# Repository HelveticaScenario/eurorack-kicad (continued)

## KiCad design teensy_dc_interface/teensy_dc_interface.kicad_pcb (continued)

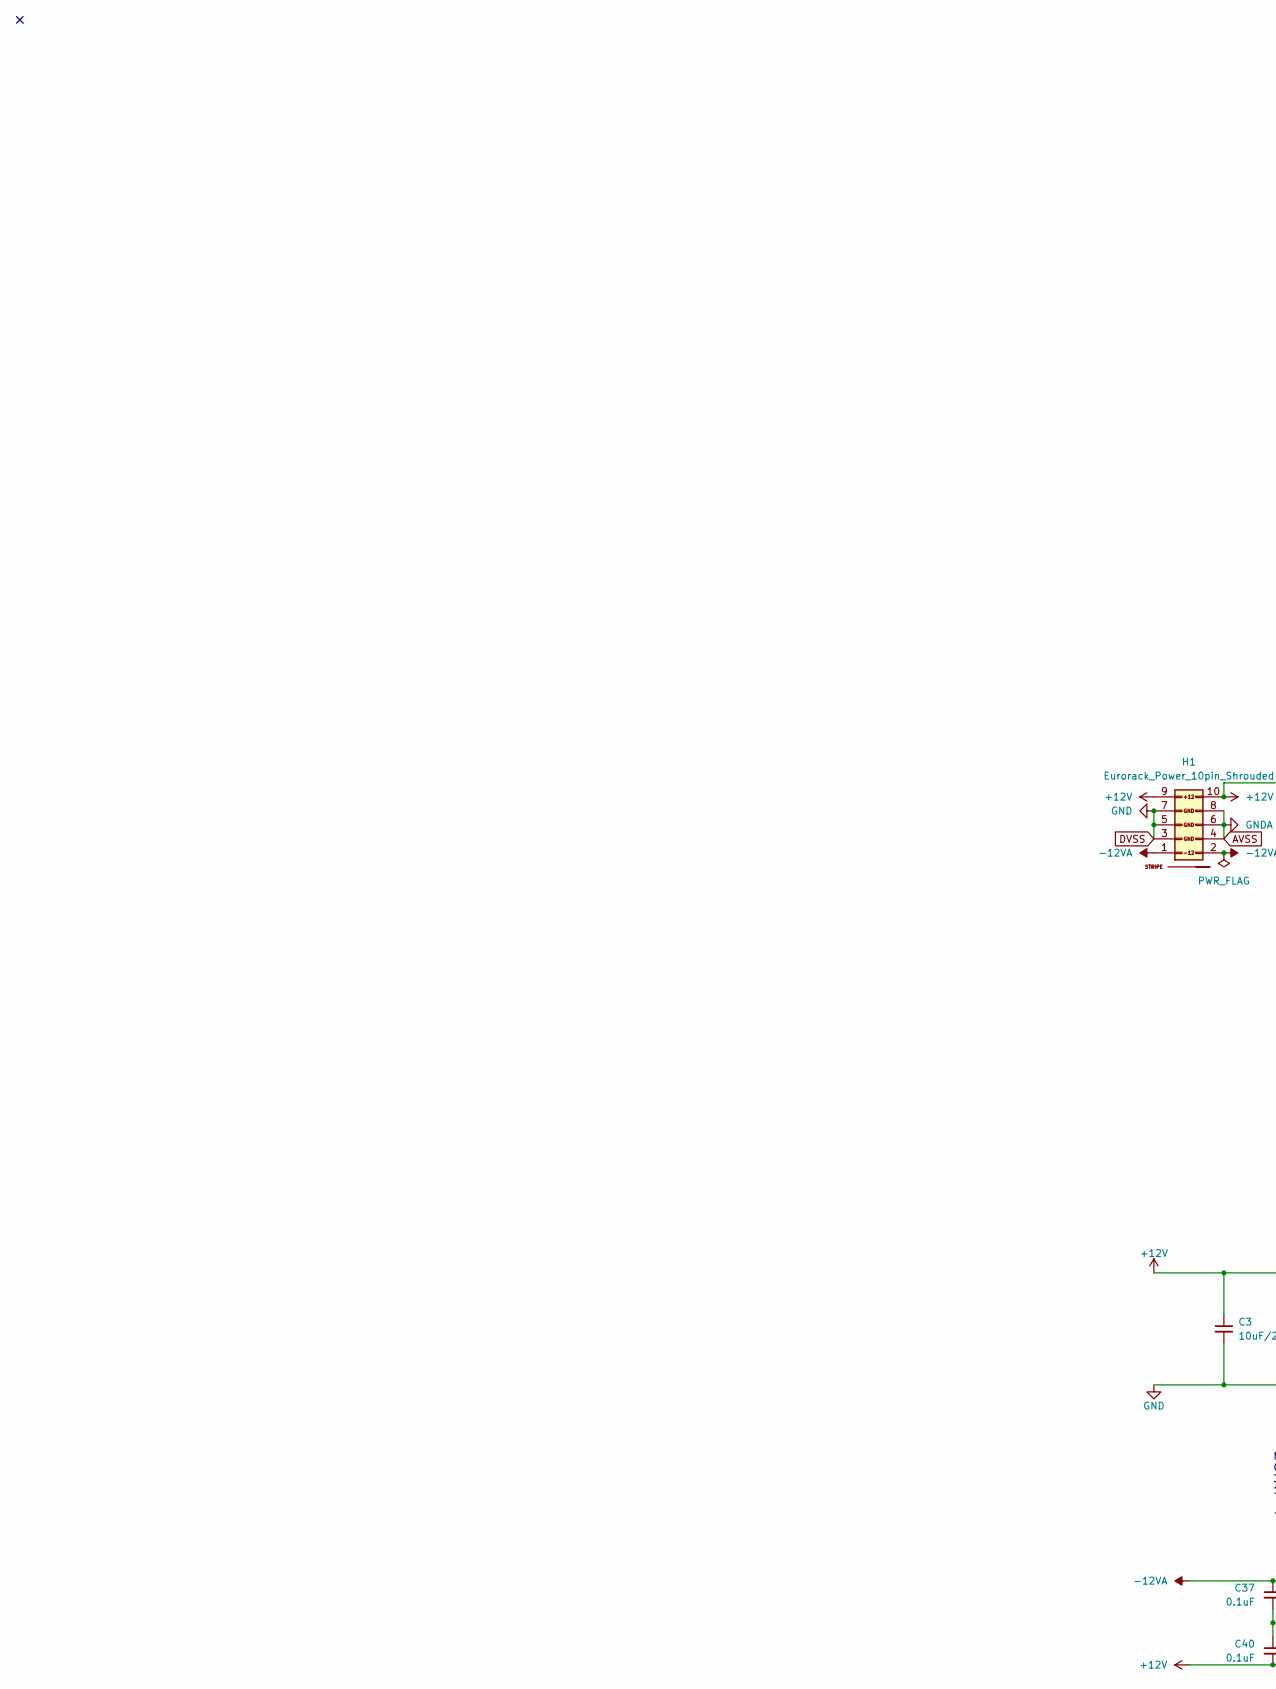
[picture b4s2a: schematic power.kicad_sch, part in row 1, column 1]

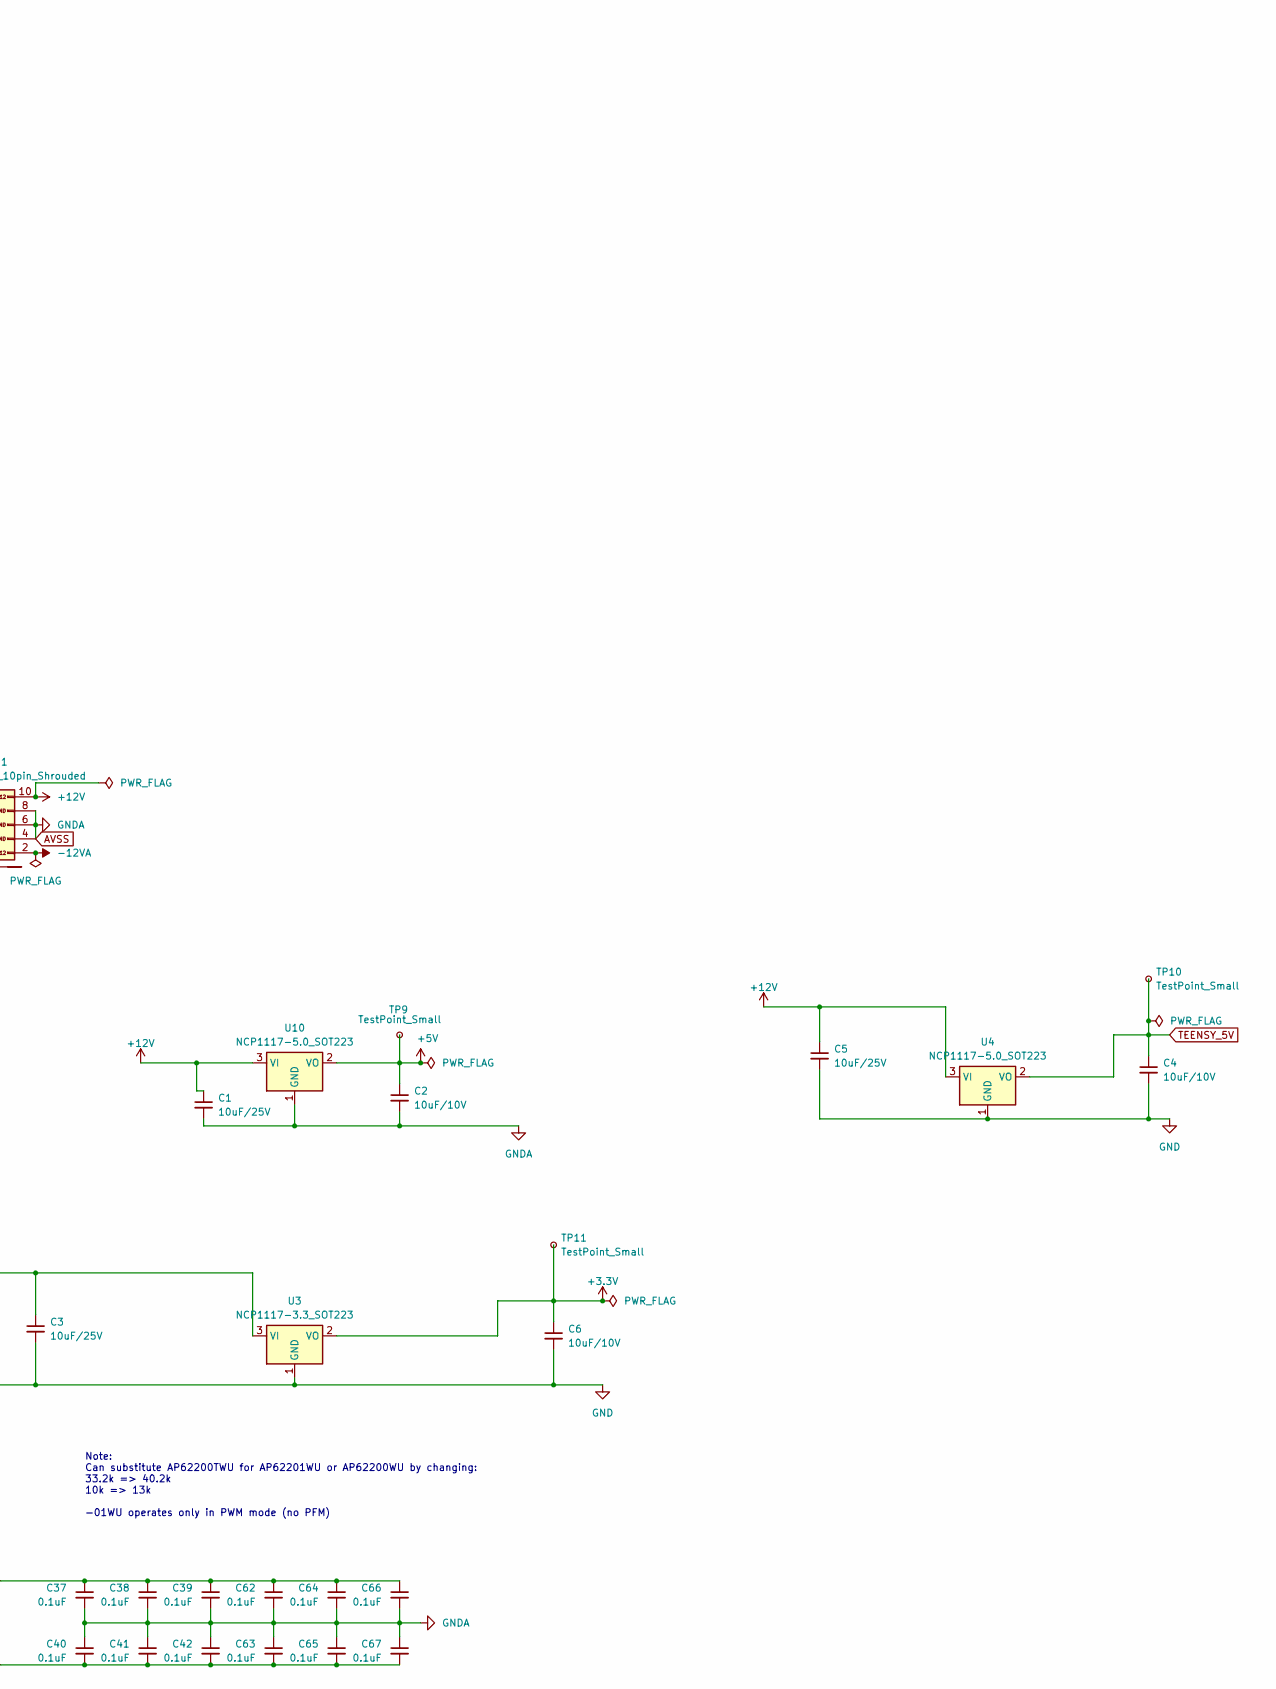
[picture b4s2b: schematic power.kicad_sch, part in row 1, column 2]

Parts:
C1, C3, C5: 10uF_0805_25V; C_0805; Part Number GRM21BR61E106MA73L; JLCPCB ID C15850
C2, C4, C6: 10uF_0603_10V; C_0603; Part Number GRM188R61A106KE69D; JLCPCB ID C19702
C37, C38, C39, C40, C41, C42, C62, C63, C64, C65, C66, C67: 0.1uF_0603_16V; C_0603; Part Number 0603YC104KAT2A; JLCPCB ID C14663
H1: Eurorack_Power_10pin_Shrouded; Pins_2x05_2.54mm_TH_EurorackPower_Shrouded; Part Number 61201021621
TP9, TP10, TP11: TestPoint_Small; TestPoint_Keystone_5005-5009_Compact
U3: NCP1117-3.3_SOT223; SOT-223-3_TabPin2
U4, U10: NCP1117-5.0_SOT223; SOT-223-3_TabPin2

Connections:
+12V: C1.1, C3.1, C5.1, C40.2, C41.2, C42.2, C63.2, C65.2, C67.2, H1.9 (+12V), H1.10 (+12V), U3.3 (VI), U4.3 (VI), U10.3 (VI); also elsewhere on the board
-12VA: C37.1, C38.1, C39.1, C62.1, C64.1, C66.1, H1.1 (-12V), H1.2 (-12V); also elsewhere on the board
AVDD: C2.1, TP9.1, U10.2 (VO); also elsewhere on the board
AVSS: C1.2, C2.2, C37.2, C38.2, C39.2, C40.1, C41.1, C42.1, C62.2, C63.1, C64.2, C65.1, C66.2, C67.1, H1.4 (GND), H1.6 (GND), H1.8 (GND), U10.1 (GND); also elsewhere on the board
DVSS: C3.2, C4.2, C5.2, C6.2, H1.3 (GND), H1.5 (GND), H1.7 (GND), U3.1 (GND), U4.1 (GND); also elsewhere on the board
TEENSY_5V: C4.1, TP10.1, U4.2 (VO); also elsewhere on the board
TVDD: C6.1, TP11.1, U3.2 (VO); also elsewhere on the board

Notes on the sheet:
Note: Can substitute AP62200TWU for AP62201WU or AP62200WU by changing: 33.2k => 40.2k 10k => 13k -01WU operates only in PWM mode (no PFM)

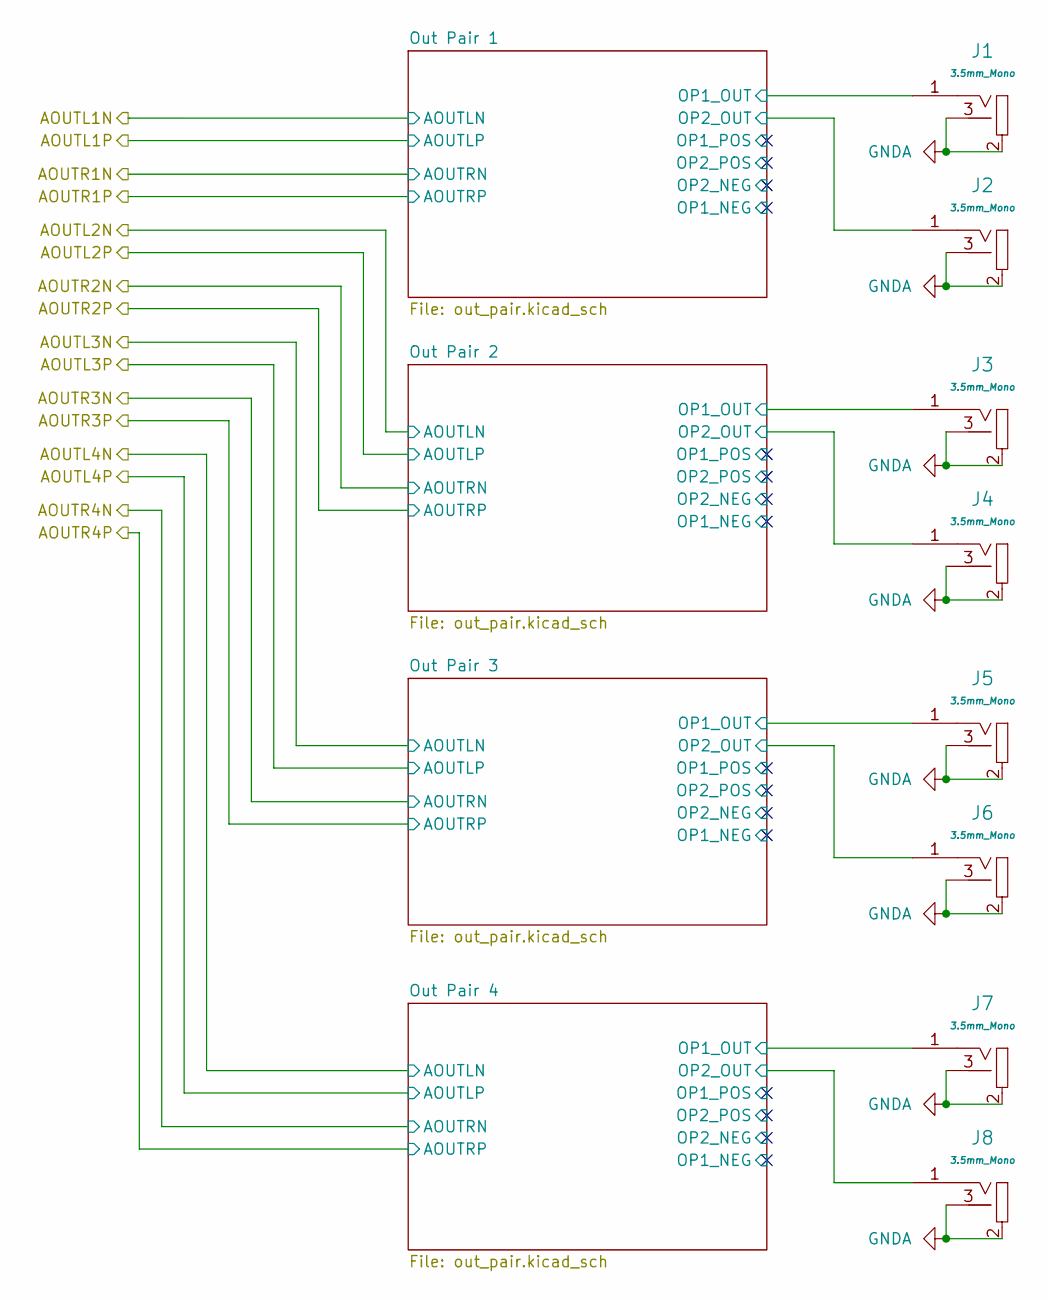
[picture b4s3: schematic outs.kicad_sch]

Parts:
J1: Chan 1 Out; EighthInch_PJ398SM; Part Number WQP-WQP518MA
J2: Chan 2 Out; EighthInch_PJ398SM; Part Number WQP-WQP518MA
J3: Chan 3 Out; EighthInch_PJ398SM; Part Number WQP-WQP518MA
J4: Chan 4 Out; EighthInch_PJ398SM; Part Number WQP-WQP518MA
J5: Chan 5 Out; EighthInch_PJ398SM; Part Number WQP-WQP518MA
J6: Chan 6 Out; EighthInch_PJ398SM; Part Number WQP-WQP518MA
J7: Chan 7 Out; EighthInch_PJ398SM; Part Number WQP-WQP518MA
J8: Chan 8 Out; EighthInch_PJ398SM; Part Number WQP-WQP518MA

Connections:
/Outs/Out Pair 1/OP1_OUT: J1.1 (SIG); also elsewhere on the board
/Outs/Out Pair 1/OP2_OUT: J2.1 (SIG); also elsewhere on the board
/Outs/Out Pair 2/OP1_OUT: J3.1 (SIG); also elsewhere on the board
/Outs/Out Pair 2/OP2_OUT: J4.1 (SIG); also elsewhere on the board
/Outs/Out Pair 3/OP1_OUT: J5.1 (SIG); also elsewhere on the board
/Outs/Out Pair 3/OP2_OUT: J6.1 (SIG); also elsewhere on the board
/Outs/Out Pair 4/OP1_OUT: J7.1 (SIG); also elsewhere on the board
/Outs/Out Pair 4/OP2_OUT: J8.1 (SIG); also elsewhere on the board
AVSS: J1.2 (SHEILD), J1.3 (SW), J2.2 (SHEILD), J2.3 (SW), J3.2 (SHEILD), J3.3 (SW), J4.2 (SHEILD), J4.3 (SW), J5.2 (SHEILD), J5.3 (SW), J6.2 (SHEILD), J6.3 (SW), J7.2 (SHEILD), J7.3 (SW), J8.2 (SHEILD), J8.3 (SW); also elsewhere on the board

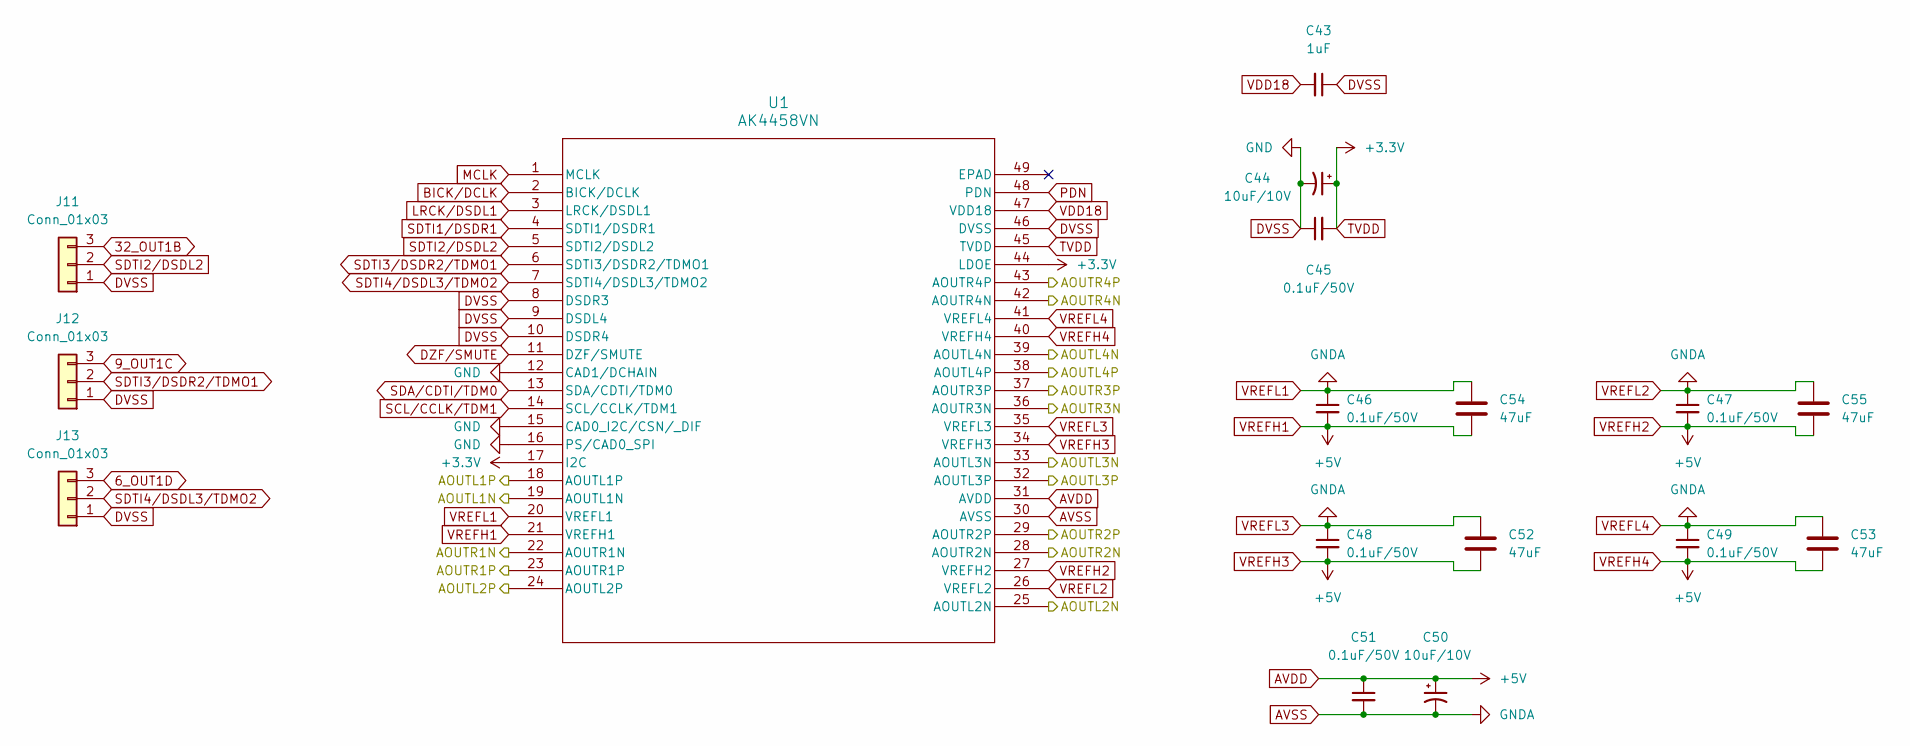
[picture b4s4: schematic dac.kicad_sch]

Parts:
C43: 1uF_0402_25V; C_0402; Part Number GMK105CC6105KV-F; JLCPCB ID C52923
C44, C50: 10uF_4x5.3_10V; CP_Elec_4x5.3; Part Number EEE-FN1A100R; JLCPCB ID C176661
C45, C46, C47, C48, C49, C51: 0.1uF_0805_50V; C_0805; Part Number GCJ21BL81H104KA01L
C52, C53, C54, C55: 47uF; C_0805_2012Metric
J11, J12, J13: Conn_01x03; Pins_1x03_2.54mm_TH; Part Number 1-0301FBV0T
U1: AK4458VN; QFN48_7x7-0p5_AKM

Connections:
6_OUT1D: J13.3; also elsewhere on the board
9_OUT1C: J12.3; also elsewhere on the board
32_OUT1B: J11.3; also elsewhere on the board
/DAC/AOUTL1N: U1.19 (AOUTL1N); also elsewhere on the board
/DAC/AOUTL1P: U1.18 (AOUTL1P); also elsewhere on the board
/DAC/AOUTL2N: U1.25 (AOUTL2N); also elsewhere on the board
/DAC/AOUTL2P: U1.24 (AOUTL2P); also elsewhere on the board
/DAC/AOUTL3N: U1.33 (AOUTL3N); also elsewhere on the board
/DAC/AOUTL3P: U1.32 (AOUTL3P); also elsewhere on the board
/DAC/AOUTL4N: U1.39 (AOUTL4N); also elsewhere on the board
/DAC/AOUTL4P: U1.38 (AOUTL4P); also elsewhere on the board
/DAC/AOUTR1N: U1.22 (AOUTR1N); also elsewhere on the board
/DAC/AOUTR1P: U1.23 (AOUTR1P); also elsewhere on the board
/DAC/AOUTR2N: U1.28 (AOUTR2N); also elsewhere on the board
/DAC/AOUTR2P: U1.29 (AOUTR2P); also elsewhere on the board
/DAC/AOUTR3N: U1.36 (AOUTR3N); also elsewhere on the board
/DAC/AOUTR3P: U1.37 (AOUTR3P); also elsewhere on the board
/DAC/AOUTR4N: U1.42 (AOUTR4N); also elsewhere on the board
/DAC/AOUTR4P: U1.43 (AOUTR4P); also elsewhere on the board
AVDD: C46.2, C47.2, C48.2, C49.2, C50.1, C51.1, C52.2, C53.2, C54.2, C55.2, U1.21 (VREFH1), U1.27 (VREFH2), U1.31 (AVDD), U1.34 (VREFH3), U1.40 (VREFH4); also elsewhere on the board
AVSS: C46.1, C47.1, C48.1, C49.1, C50.2, C51.2, C52.1, C53.1, C54.1, C55.1, U1.20 (VREFL1), U1.26 (VREFL2), U1.30 (AVSS), U1.35 (VREFL3), U1.41 (VREFL4); also elsewhere on the board
BICK/DCLK: U1.2 (BICK/DCLK); also elsewhere on the board
DVSS: C43.1, C44.2, C45.1, J11.1, J12.1, J13.1, U1.8 (DSDR3), U1.9 (DSDL4), U1.10 (DSDR4), U1.12 (CAD1/DCHAIN), U1.15 (CAD0_I2C/CSN/_DIF), U1.16 (PS/CAD0_SPI), U1.46 (DVSS); also elsewhere on the board
DZF/SMUTE: U1.11 (DZF/SMUTE)
LRCK/DSDL1: U1.3 (LRCK/DSDL1); also elsewhere on the board
MCLK: U1.1 (MCLK); also elsewhere on the board
PDN: U1.48 (PDN); also elsewhere on the board
SCL/CCLK/TDM1: U1.14 (SCL/CCLK/TDM1); also elsewhere on the board
SDA/CDTI/TDM0: U1.13 (SDA/CDTI/TDM0); also elsewhere on the board
SDTI1/DSDR1: U1.4 (SDTI1/DSDR1); also elsewhere on the board
SDTI2/DSDL2: J11.2, U1.5 (SDTI2/DSDL2)
SDTI3/DSDR2/TDMO1: J12.2, U1.6 (SDTI3/DSDR2/TDMO1)
SDTI4/DSDL3/TDMO2: J13.2, U1.7 (SDTI4/DSDL3/TDMO2)
TVDD: C44.1, C45.2, U1.17 (I2C), U1.44 (LDOE), U1.45 (TVDD); also elsewhere on the board
VDD18: C43.2, U1.47 (VDD18)

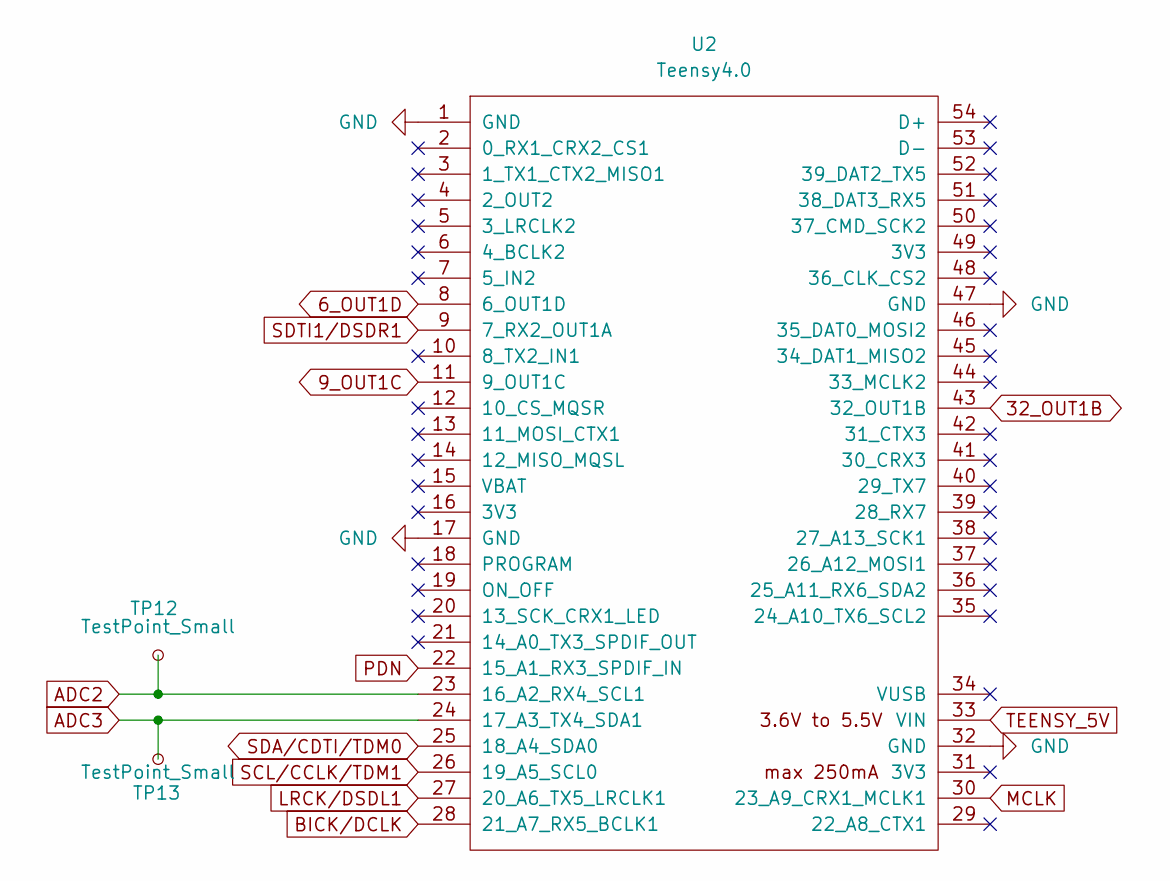
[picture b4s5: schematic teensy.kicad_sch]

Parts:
TP12, TP13: TestPoint_Small; TestPoint_Keystone_5005-5009_Compact
U2: Teensy4.0; Teensy40_SMT

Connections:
6_OUT1D: U2.8 (6_OUT1D); also elsewhere on the board
9_OUT1C: U2.11 (9_OUT1C); also elsewhere on the board
32_OUT1B: U2.43 (32_OUT1B); also elsewhere on the board
ADC2: TP12.1, U2.23 (16_A2_RX4_SCL1); also elsewhere on the board
ADC3: TP13.1, U2.24 (17_A3_TX4_SDA1); also elsewhere on the board
BICK/DCLK: U2.28 (21_A7_RX5_BCLK1); also elsewhere on the board
DVSS: U2.1 (GND), U2.17 (GND), U2.32 (GND), U2.47 (GND); also elsewhere on the board
LRCK/DSDL1: U2.27 (20_A6_TX5_LRCLK1); also elsewhere on the board
MCLK: U2.30 (23_A9_CRX1_MCLK1); also elsewhere on the board
PDN: U2.22 (15_A1_RX3_SPDIF_IN); also elsewhere on the board
SCL/CCLK/TDM1: U2.26 (19_A5_SCL0); also elsewhere on the board
SDA/CDTI/TDM0: U2.25 (18_A4_SDA0); also elsewhere on the board
SDTI1/DSDR1: U2.9 (7_RX2_OUT1A); also elsewhere on the board
TEENSY_5V: U2.33 (VIN); also elsewhere on the board

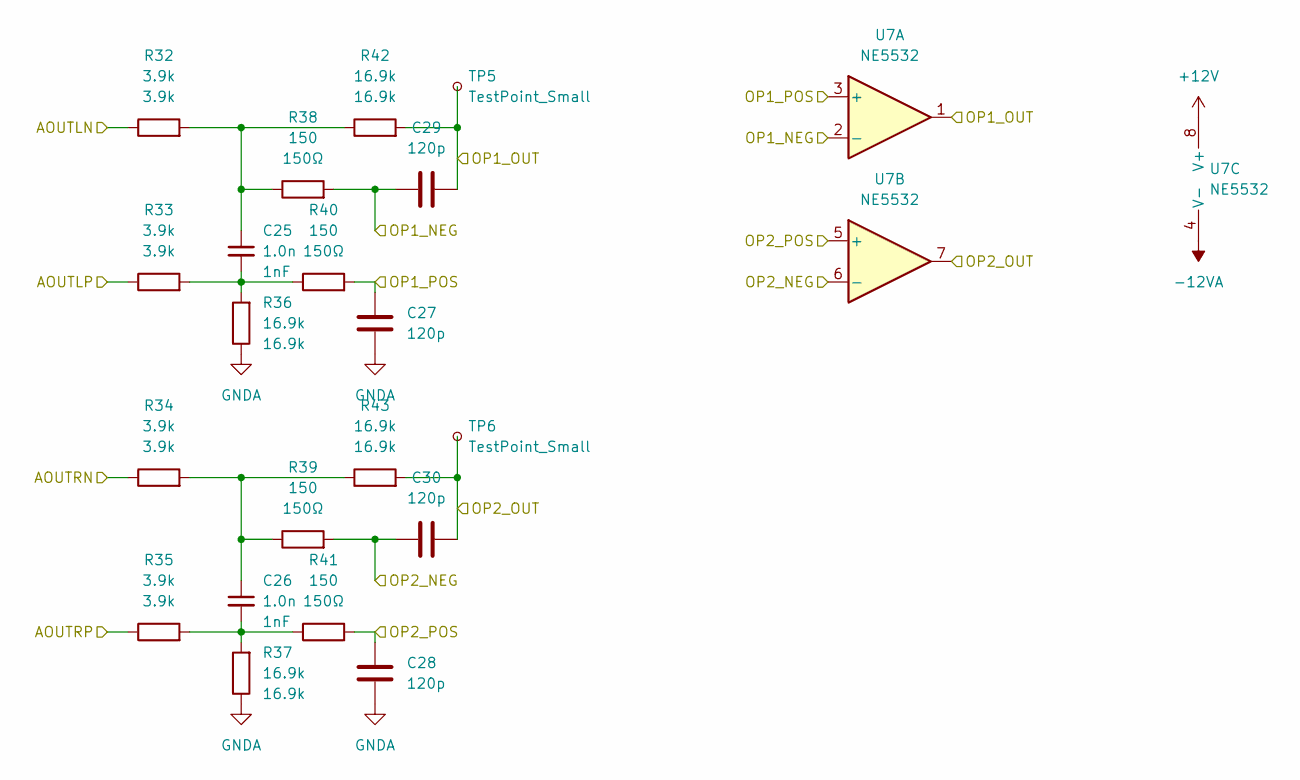
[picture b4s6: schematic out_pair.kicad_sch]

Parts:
C25, C26: 1.0n; C_0402; Part Number 04025C102KAT2A; JLCPCB ID C167632
C27, C28, C29, C30: 120p; C_0402
R32, R33, R34, R35: 3.9k; R_0402; Part Number RC0402FR-073K9L; JLCPCB ID C131467
R36, R37, R42, R43: 16.9k; R_0402; Part Number RC0402FR-0716K9L; JLCPCB ID C163488
R38, R39, R40, R41: 150; R_0402; Part Number RC0402FR-07150RL; JLCPCB ID C138054
TP5, TP6: TestPoint_Small; TestPoint_Keystone_5005-5009_Compact
U7: NE5532; SOIC127P599X175-8N

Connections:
+12V: U7.8 (V+); also elsewhere on the board
-12VA: U7.4 (V-); also elsewhere on the board
/DAC/AOUTL3N: R32.1; also elsewhere on the board
/DAC/AOUTL3P: R33.1; also elsewhere on the board
/DAC/AOUTR3N: R34.1; also elsewhere on the board
/DAC/AOUTR3P: R35.1; also elsewhere on the board
/Outs/Out Pair 3/OP1_NEG: C29.1, R38.2, U7.2 (-)
/Outs/Out Pair 3/OP1_OUT: C29.2, R42.2, TP5.1, U7.1; also elsewhere on the board
/Outs/Out Pair 3/OP1_POS: C27.1, R40.2, U7.3 (+)
/Outs/Out Pair 3/OP2_NEG: C30.1, R39.2, U7.6 (-)
/Outs/Out Pair 3/OP2_OUT: C30.2, R43.2, TP6.1, U7.7; also elsewhere on the board
/Outs/Out Pair 3/OP2_POS: C28.1, R41.2, U7.5 (+)
AVSS: C27.2, C28.2, R36.1, R37.1; also elsewhere on the board
unnamed: C25.1, R32.2, R38.1, R42.1
unnamed: C25.2, R33.2, R36.2, R40.1
unnamed: C26.1, R34.2, R39.1, R43.1
unnamed: C26.2, R35.2, R37.2, R41.1

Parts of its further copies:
C13, C16, C19, C20, C31, C32: 1.0n; C_0402; Part Number 04025C102KAT2A; JLCPCB ID C167632
C14, C15, C17, C18, C21, C22, C23, C24, C33, C34, C35, C36: 120p; C_0402
R8, R9, R14, R15, R20, R21, R22, R23, R44, R45, R46, R47: 3.9k; R_0402; Part Number RC0402FR-073K9L; JLCPCB ID C131467
R10, R13, R16, R19, R24, R25, R30, R31, R48, R49, R54, R55: 16.9k; R_0402; Part Number RC0402FR-0716K9L; JLCPCB ID C163488
R11, R12, R17, R18, R26, R27, R28, R29, R50, R51, R52, R53: 150; R_0402; Part Number RC0402FR-07150RL; JLCPCB ID C138054
TP1, TP2, TP3, TP4, TP7, TP8: TestPoint_Small; TestPoint_Keystone_5005-5009_Compact
U5, U6, U8: NE5532; SOIC127P599X175-8N

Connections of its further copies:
+12V: U5.8 (V+), U6.8 (V+), U8.8 (V+); also elsewhere on the board
-12VA: U5.4 (V-), U6.4 (V-), U8.4 (V-); also elsewhere on the board
/DAC/AOUTL1N: R8.1; also elsewhere on the board
/DAC/AOUTL1P: R9.1; also elsewhere on the board
/DAC/AOUTL2N: R20.1; also elsewhere on the board
/DAC/AOUTL2P: R21.1; also elsewhere on the board
/DAC/AOUTL4N: R44.1; also elsewhere on the board
/DAC/AOUTL4P: R45.1; also elsewhere on the board
/DAC/AOUTR1N: R14.1; also elsewhere on the board
/DAC/AOUTR1P: R15.1; also elsewhere on the board
/DAC/AOUTR2N: R22.1; also elsewhere on the board
/DAC/AOUTR2P: R23.1; also elsewhere on the board
/DAC/AOUTR4N: R46.1; also elsewhere on the board
/DAC/AOUTR4P: R47.1; also elsewhere on the board
/Outs/Out Pair 1/OP1_NEG: C15.1, R11.2, U5.2 (-)
/Outs/Out Pair 1/OP1_OUT: C15.2, R13.2, TP1.1, U5.1; also elsewhere on the board
/Outs/Out Pair 1/OP1_POS: C14.1, R12.2, U5.3 (+)
/Outs/Out Pair 1/OP2_NEG: C18.1, R17.2, U5.6 (-)
/Outs/Out Pair 1/OP2_OUT: C18.2, R19.2, TP2.1, U5.7; also elsewhere on the board
/Outs/Out Pair 1/OP2_POS: C17.1, R18.2, U5.5 (+)
/Outs/Out Pair 2/OP1_NEG: C23.1, R26.2, U6.2 (-)
/Outs/Out Pair 2/OP1_OUT: C23.2, R30.2, TP3.1, U6.1; also elsewhere on the board
/Outs/Out Pair 2/OP1_POS: C21.1, R28.2, U6.3 (+)
/Outs/Out Pair 2/OP2_NEG: C24.1, R27.2, U6.6 (-)
/Outs/Out Pair 2/OP2_OUT: C24.2, R31.2, TP4.1, U6.7; also elsewhere on the board
/Outs/Out Pair 2/OP2_POS: C22.1, R29.2, U6.5 (+)
/Outs/Out Pair 4/OP1_NEG: C35.1, R50.2, U8.2 (-)
/Outs/Out Pair 4/OP1_OUT: C35.2, R54.2, TP7.1, U8.1; also elsewhere on the board
/Outs/Out Pair 4/OP1_POS: C33.1, R52.2, U8.3 (+)
/Outs/Out Pair 4/OP2_NEG: C36.1, R51.2, U8.6 (-)
/Outs/Out Pair 4/OP2_OUT: C36.2, R55.2, TP8.1, U8.7; also elsewhere on the board
/Outs/Out Pair 4/OP2_POS: C34.1, R53.2, U8.5 (+)
AVSS: C14.2, C17.2, C21.2, C22.2, C33.2, C34.2, R10.1, R16.1, R24.1, R25.1, R48.1, R49.1; also elsewhere on the board
unnamed: C13.1, R8.2, R11.1, R13.1
unnamed: C13.2, R9.2, R10.2, R12.1
unnamed: C16.1, R14.2, R17.1, R19.1
unnamed: C16.2, R15.2, R16.2, R18.1
unnamed: C19.1, R20.2, R26.1, R30.1
unnamed: C19.2, R21.2, R24.2, R28.1
unnamed: C20.1, R22.2, R27.1, R31.1
unnamed: C20.2, R23.2, R25.2, R29.1
unnamed: C31.1, R44.2, R50.1, R54.1
unnamed: C31.2, R45.2, R48.2, R52.1
unnamed: C32.1, R46.2, R51.1, R55.1
unnamed: C32.2, R47.2, R49.2, R53.1

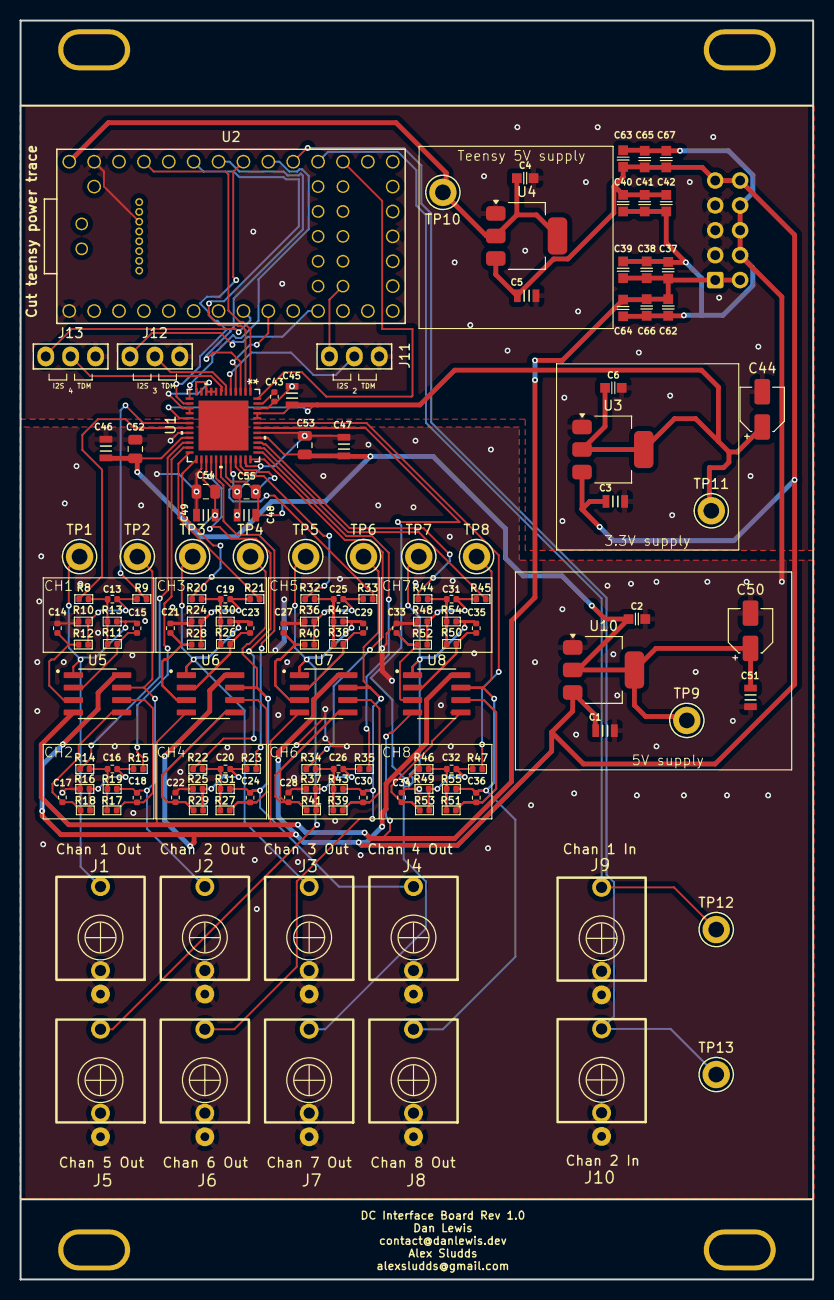
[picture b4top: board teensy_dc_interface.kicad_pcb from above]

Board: 2 copper layers, 80.9 x 128.5 mm, 143 parts (1 on the bottom side), 79 nets.

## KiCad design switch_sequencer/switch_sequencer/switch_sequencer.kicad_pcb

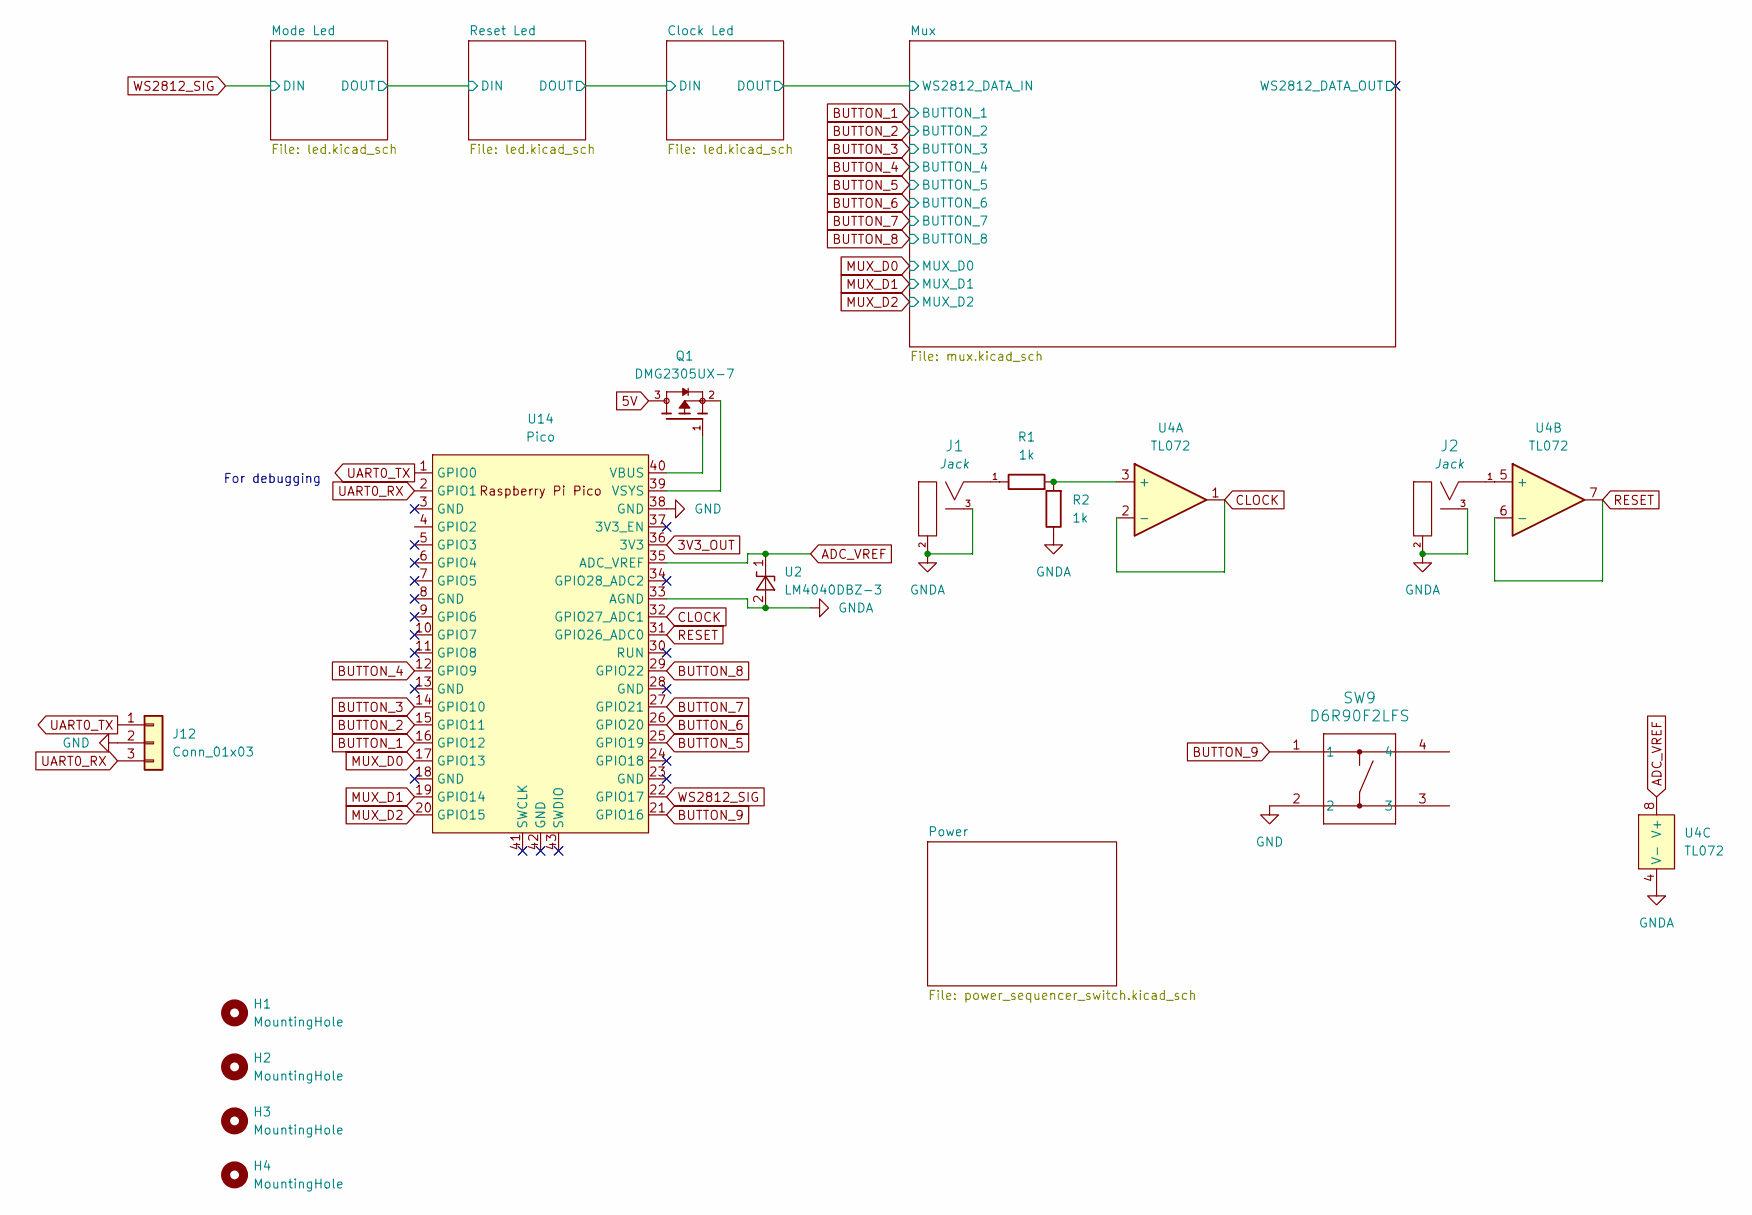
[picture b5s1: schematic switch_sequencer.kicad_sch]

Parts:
H1, H2, H3, H4: MountingHole; Faceplate_Rail_Mount_Slot_Plated
J1, J2: 3.5mm_Mono_Switched_sm; EighthInch_PJ398SM; Part Number WQP-WQP518MA
J12: Conn_01x03; Pins_1x03_2.54mm_TH; Part Number 1-0301FBV0T
Q1: DMG2305UX-7; SOT91P240X110-3N_DMG2305UX-7; PARTREV 09/2018
R1, R2: 1k_0402; R_0402; Part Number RC0402FR-071KL; JLCPCB ID C106235
SW9: D6R90F2LFS; D6R90_CNK
U2: LM4040DBZ-3; SOT-23
U4: TL072; TSSOP-8_4.4x3mm_Pitch0.65mm; JLCPCB ID C90748
U14: Pico; RPi_Pico_SMD_TH

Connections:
3V3_OUT: U14.36 (3V3)
5V: Q1.3; also elsewhere on the board
ADC_VREF: U2.1 (K), U4.8 (V+), U14.35 (ADC_VREF)
BUTTON_1: U14.16 (GPIO12); also elsewhere on the board
BUTTON_2: U14.15 (GPIO11); also elsewhere on the board
BUTTON_3: U14.14 (GPIO10); also elsewhere on the board
BUTTON_4: U14.12 (GPIO9); also elsewhere on the board
BUTTON_5: U14.25 (GPIO19); also elsewhere on the board
BUTTON_6: U14.26 (GPIO20); also elsewhere on the board
BUTTON_7: U14.27 (GPIO21); also elsewhere on the board
BUTTON_8: U14.29 (GPIO22); also elsewhere on the board
BUTTON_9: SW9.1, U14.21 (GPIO16)
CLOCK: U4.1, U4.2 (-), U14.32 (GPIO27_ADC1)
GND: J12.2, SW9.2, U14.38 (GND); also elsewhere on the board
GNDA: J1.2 (SHEILD), J1.3 (SW), J2.2 (SHEILD), J2.3 (SW), R2.1, U2.2 (A), U4.4 (V-), U14.33 (AGND)
MUX_D0: U14.17 (GPIO13); also elsewhere on the board
MUX_D1: U14.19 (GPIO14); also elsewhere on the board
MUX_D2: U14.20 (GPIO15); also elsewhere on the board
unnamed: J1.1 (SIG), R1.1
unnamed: J2.1 (SIG), U4.5 (+)
unnamed: R1.2, R2.2, U4.3 (+)
unnamed: Q1.1, U14.40 (VBUS)
unnamed: Q1.2, U14.39 (VSYS)
RESET: U4.6 (-), U4.7, U14.31 (GPIO26_ADC0)
UART0_RX: J12.3, U14.2 (GPIO1)
UART0_TX: J12.1, U14.1 (GPIO0)
WS2812_SIG: U14.22 (GPIO17); also elsewhere on the board

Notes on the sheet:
For debugging

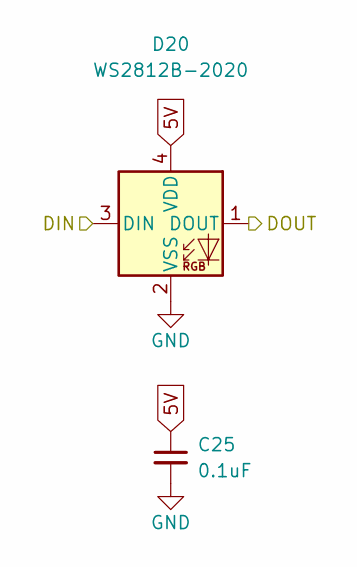
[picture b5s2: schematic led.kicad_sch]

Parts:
C25: 100nF_0402_16V; C_0402; Part Number GCM155R71C104KA55D; JLCPCB ID C1525
D20: WS2812B-2020; LED_WS2812B-2020_PLCC4_2.0x2.0mm

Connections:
5V: C25.1, D20.4 (VDD); also elsewhere on the board
/Mode Led/DOUT: D20.1 (DOUT); also elsewhere on the board
GND: C25.2, D20.2 (VSS); also elsewhere on the board
WS2812_SIG: D20.3 (DIN); also elsewhere on the board

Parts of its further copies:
C15, C16, C17, C18, C19, C20, C21, C22, C23, C24: 100nF_0402_16V; C_0402; Part Number GCM155R71C104KA55D; JLCPCB ID C1525
D2, D4, D6, D8, D10, D12, D14, D16, D18, D19: WS2812B-2020; LED_WS2812B-2020_PLCC4_2.0x2.0mm

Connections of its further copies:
5V: C15.1, C16.1, C17.1, C18.1, C19.1, C20.1, C21.1, C22.1, C23.1, C24.1, D2.4 (VDD), D4.4 (VDD), D6.4 (VDD), D8.4 (VDD), D10.4 (VDD), D12.4 (VDD), D14.4 (VDD), D16.4 (VDD), D18.4 (VDD), D19.4 (VDD); also elsewhere on the board
/Clock Led/DIN: D18.3 (DIN), D19.1 (DOUT)
/Clock Led/DOUT: D2.3 (DIN), D18.1 (DOUT)
/Mode Led/DOUT: D19.3 (DIN); also elsewhere on the board
/Mux/Signal 1/LED_DOUT: D2.1 (DOUT), D4.3 (DIN)
/Mux/Signal 2/LED_DOUT: D4.1 (DOUT), D6.3 (DIN)
/Mux/Signal 3/LED_DOUT: D6.1 (DOUT), D8.3 (DIN)
/Mux/Signal 4/LED_DOUT: D8.1 (DOUT), D10.3 (DIN)
/Mux/Signal 5/LED_DOUT: D10.1 (DOUT), D12.3 (DIN)
/Mux/Signal 6/LED_DOUT: D12.1 (DOUT), D14.3 (DIN)
/Mux/Signal 7/LED_DOUT: D14.1 (DOUT), D16.3 (DIN)
/Mux/WS2812_DATA_OUT: D16.1 (DOUT)
GND: C15.2, C16.2, C17.2, C18.2, C19.2, C20.2, C21.2, C22.2, C23.2, C24.2, D2.2 (VSS), D4.2 (VSS), D6.2 (VSS), D8.2 (VSS), D10.2 (VSS), D12.2 (VSS), D14.2 (VSS), D16.2 (VSS), D18.2 (VSS), D19.2 (VSS); also elsewhere on the board

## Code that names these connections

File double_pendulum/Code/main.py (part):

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from array import array

# PIN definitions
SDI_DAC = 19
SCK_DAC = 18
CS_DAC1 = 17
CS_DAC2 = 16
SDA_DISPLAY = 15
SCL_DISPLAY = 14
CS_DISPLAY  = 13
DC_DISPLAY  = 12
BUTTON4     = 10
BUTTON3     = 9
RES_DISPLAY = 21
BUTTON2     = 7
BUTTON1     = 6
MUXCTL2     = 5
MUXCTL1     = 4
MUXCTL0     = 3
IN1         = 26
IN2         = 27
IN3         = 28

CS_DAC1_PIN = Pin(CS_DAC1, Pin.OUT)
CS_DAC2_PIN = Pin(CS_DAC2, Pin.OUT)

# Example usage
dac = MCP4922(
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    mosi = SDI_DAC,
)

dac.setVoltage_gain(0,1, CS_DAC1_PIN)
dac.setVoltage_gain(0,1, CS_DAC2_PIN)

dac.setVoltage(0, int(512), CS_DAC1_PIN)
dac.setVoltage(1, int(256), CS_DAC1_PIN)

dac.setVoltage(0, int(457), CS_DAC2_PIN)
dac.setVoltage(1, int(987), CS_DAC2_PIN)
    # sleep(1)   

# pin = Pin("LED", Pin.OUT)
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
class RoundLCD(framebuf.FrameBuffer):
    def __init__(self):
        self.dc = Pin(DC_DISPLAY, Pin.OUT)
        self.cs = Pin(CS_DISPLAY, Pin.OUT)
        self.sck = Pin(SCL_DISPLAY, Pin.OUT)
        self.mosi = Pin(SDA_DISPLAY, Pin.OUT)
        self.rst = Pin(RES_DISPLAY, Pin.OUT)
        self.cs(1)
        self.spi = SPI(1, baudrate=200_000_000, polarity=0, phase=0, sck=self.sck, mosi=self.mosi,miso=None)
        self.dc(1)
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
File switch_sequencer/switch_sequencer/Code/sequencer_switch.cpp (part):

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#include "stdlib.h"
#include "ws2812.pio.h"

#define MUX_D0_PIN 13
#define MUX_D1_PIN 14
#define MUX_D2_PIN 15

#define BUTTON_1_PIN 12
#define BUTTON_2_PIN 11
#define BUTTON_3_PIN 10
#define BUTTON_4_PIN 9
#define BUTTON_5_PIN 19
#define BUTTON_6_PIN 20
#define BUTTON_7_PIN 21
#define BUTTON_8_PIN 22
#define BUTTON_9_PIN 16

#define CLOCK_PIN 27
#define RESET_PIN 26
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
void set_switch_state()
{
    gpio_put(MUX_D0_PIN, switch_state & 0x01);
    gpio_put(MUX_D1_PIN, (switch_state & 0x02) >> 1);
    gpio_put(MUX_D2_PIN, (switch_state & 0x04) >> 2);
}

/* Encoder Callback*/
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    // gpio_set_irq_enabled(ENC_A, GPIO_IRQ_EDGE_FALL, true);
    // gpio_set_irq_enabled(ENC_B, GPIO_IRQ_EDGE_FALL, true);

    gpio_init(MUX_D0_PIN);
    gpio_init(MUX_D1_PIN);
    gpio_init(MUX_D2_PIN);
    gpio_set_dir(MUX_D0_PIN, GPIO_OUT);
    gpio_set_dir(MUX_D1_PIN, GPIO_OUT);
    gpio_set_dir(MUX_D2_PIN, GPIO_OUT);

    gpio_init(CLOCK_PIN);
    gpio_set_dir(CLOCK_PIN, GPIO_IN);
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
